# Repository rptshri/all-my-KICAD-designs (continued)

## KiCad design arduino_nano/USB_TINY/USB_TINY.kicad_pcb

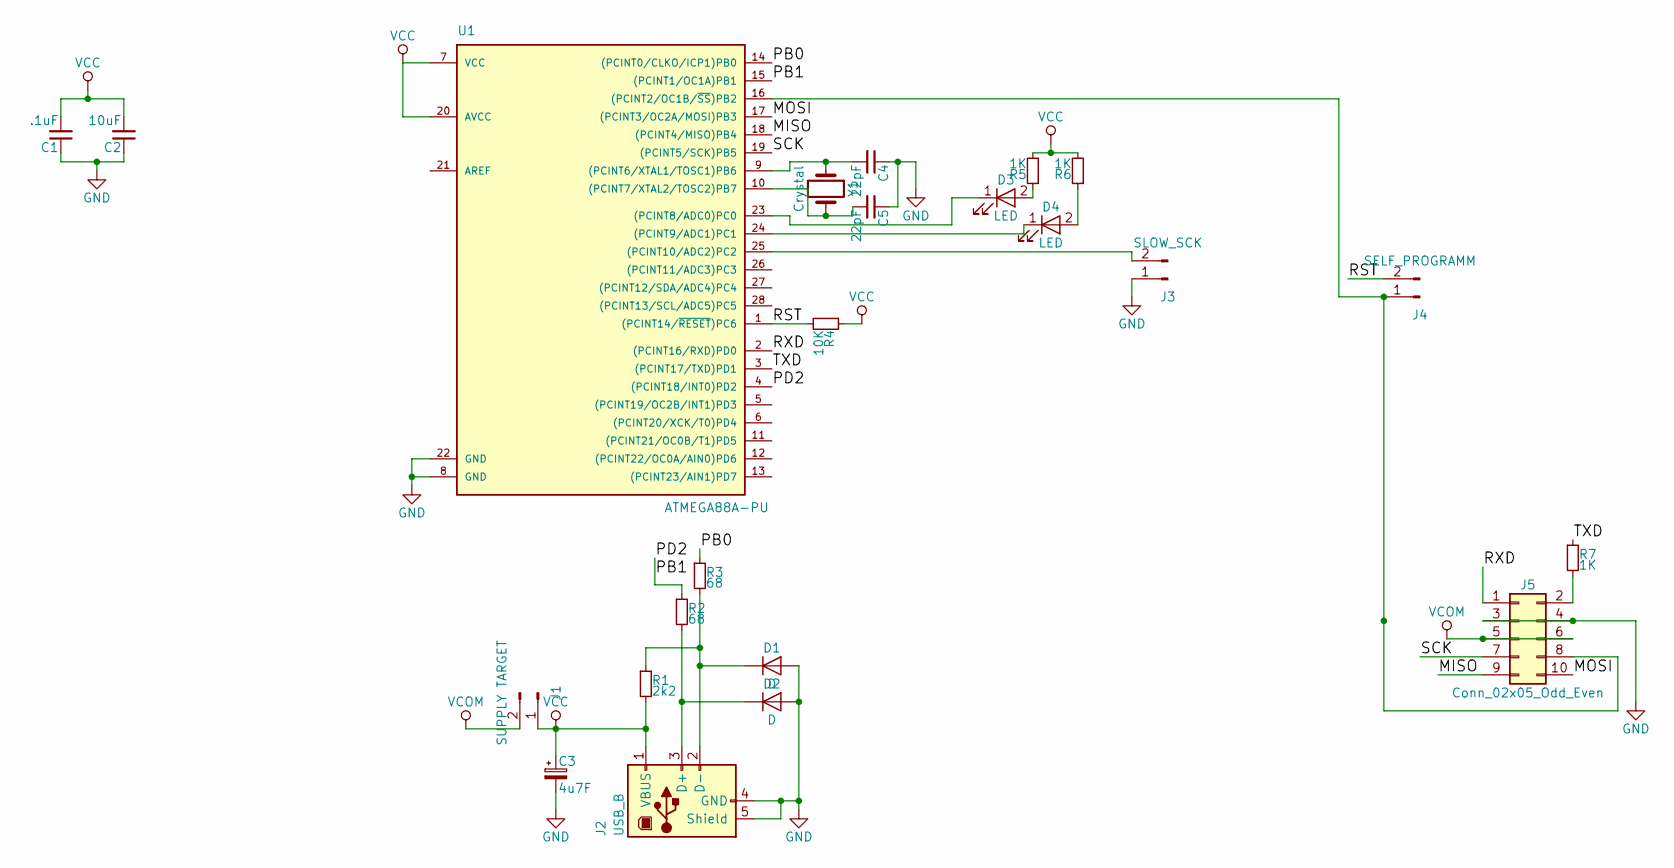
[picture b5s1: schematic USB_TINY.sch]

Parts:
C1: .1uF; C_Disc_D3.4mm_W2.1mm_P2.50mm
C2: 10uF; C_Disc_D3.4mm_W2.1mm_P2.50mm
C3: 4u7F; CP_Radial_D4.0mm_P2.00mm
C4, C5: 22pF; C_Disc_D3.0mm_W2.0mm_P2.50mm
D1, D2: D; D_A-405_P7.62mm_Horizontal
D3, D4: LED; LED_D3.0mm
J1: SUPPLY TARGET; Pin_Header_Straight_1x02_Pitch2.54mm
J2: USB_B
J3: SLOW_SCK; Pin_Header_Straight_1x02_Pitch2.54mm
J4: SELF_PROGRAMM; Pin_Header_Straight_1x02_Pitch2.54mm
J5: Conn_02x05_Odd_Even; Pin_Header_Straight_2x05_Pitch2.54mm
R1: 2k2; R_Axial_DIN0207_L6.3mm_D2.5mm_P7.62mm_Horizontal
R2, R3: 68; R_Axial_DIN0207_L6.3mm_D2.5mm_P7.62mm_Horizontal
R4: 10K; R_Axial_DIN0207_L6.3mm_D2.5mm_P7.62mm_Horizontal
R5, R6, R7: 1K; R_Axial_DIN0207_L6.3mm_D2.5mm_P7.62mm_Horizontal
U1: ATMEGA88A-PU; DIP-28_W7.62mm_LongPads
Y1: Crystal; Crystal_HC18-U_Vertical

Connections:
/MISO: J5.9, U1.18 ((PCINT4/MISO)PB4)
/MOSI: J5.10, U1.17 ((PCINT3/OC2A/MOSI)PB3)
/PB0: R3.1, U1.14 ((PCINT0/CLKO/ICP1)PB0)
/PB1: R2.1, U1.4 ((PCINT18/INT0)PD2), U1.15 ((PCINT1/OC1A)PB1)
/RST: J4.2, R4.2, U1.1 ((PCINT14/~RESET~)PC6)
/RXD: J5.1, U1.2 ((PCINT16/RXD)PD0)
/SCK: J5.7, U1.19 ((PCINT5/SCK)PB5)
/TXD: R7.1, U1.3 ((PCINT17/TXD)PD1)
GND: C1.1, C2.1, C3.2, C4.1, C5.1, D1.2 (A), D2.2 (A), J2.4 (GND), J2.5 (Shield), J3.1, J5.3, J5.4, U1.8 (GND), U1.22 (GND)
unnamed: C4.2, U1.9 ((PCINT6/XTAL1/TOSC1)PB6), Y1.1
unnamed: C5.2, U1.10 ((PCINT7/XTAL2/TOSC2)PB7), Y1.2
unnamed: D1.1 (K), J2.2 (D-), R1.1, R3.2
unnamed: D2.1 (K), J2.3 (D+), R2.2
unnamed: D3.1 (K), U1.23 ((PCINT8/ADC0)PC0)
unnamed: D3.2 (A), R5.1
unnamed: D4.1 (K), U1.24 ((PCINT9/ADC1)PC1)
unnamed: D4.2 (A), R6.1
unnamed: J3.2, U1.25 ((PCINT10/ADC2)PC2)
unnamed: J4.1, J5.8, U1.16 ((PCINT2/OC1B/~SS~)PB2)
unnamed: J5.2, R7.2
VCC: C1.2, C2.2, C3.1, J1.1, J2.1 (VBUS), R1.2, R4.1, R5.2, R6.2, U1.7 (VCC), U1.20 (AVCC)
VCOM: J1.2, J5.5, J5.6

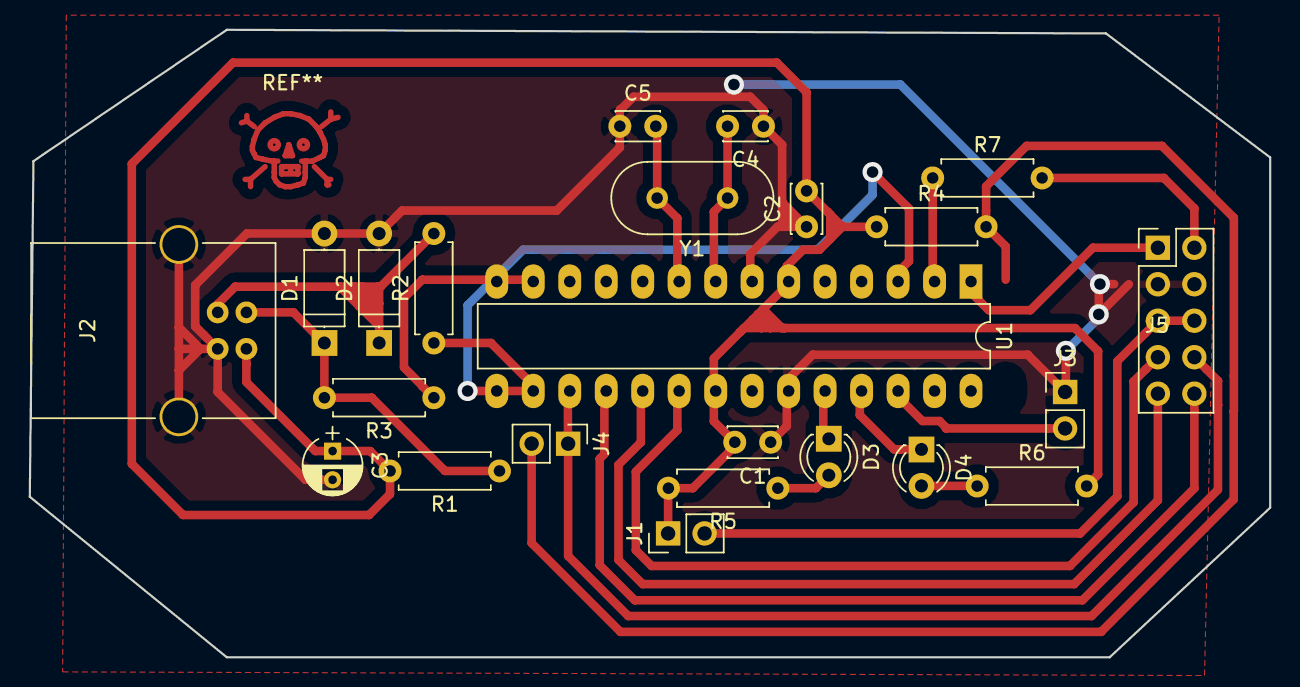
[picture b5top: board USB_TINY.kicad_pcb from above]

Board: 2 copper layers, 86.4 x 43.7 mm, 23 parts (0 on the bottom side), 22 nets.

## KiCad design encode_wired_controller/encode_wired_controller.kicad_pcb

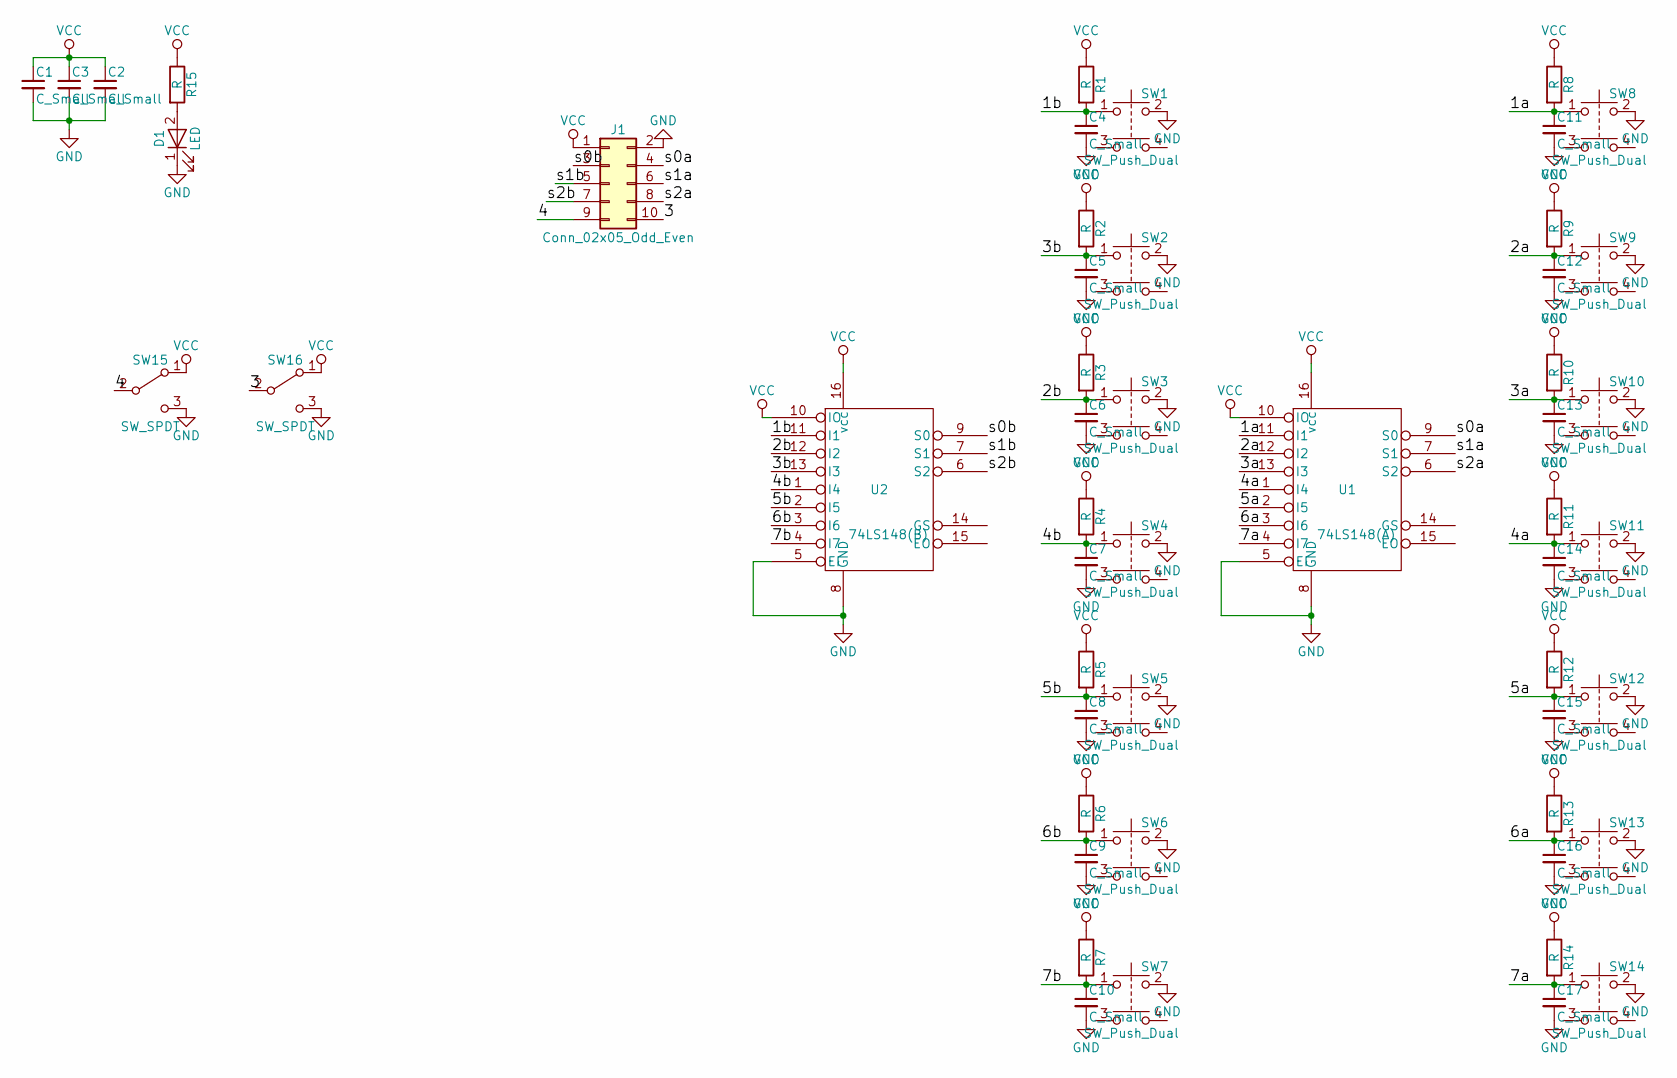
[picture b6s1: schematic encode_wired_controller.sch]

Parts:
C1, C2, C3, C4, C5, C6, C7, C8, C9, C10, C11, C12, C13, C14, C15, C16, C17: C_Small; C_Disc_D3.4mm_W2.1mm_P2.50mm
D1: LED; LED_D5.0mm_FlatTop
J1: Conn_02x05_Odd_Even; Pin_Header_Angled_2x05_Pitch2.54mm
R1, R2, R3, R4, R5, R6, R7, R8, R9, R10, R11, R12, R13, R14, R15: R; R_Axial_DIN0207_L6.3mm_D2.5mm_P7.62mm_Horizontal
SW1, SW2, SW3, SW4, SW5, SW6, SW7, SW8, SW9, SW10, SW11, SW12, SW13, SW14: SW_Push_Dual; SW_PUSH_6mm_h5mm
SW15, SW16: SW_SPDT; SW_E-Switch_EG1224_SPDT_Angled
U1: 74LS148(A); DIP-16_W7.62mm_LongPads
U2: 74LS148(B); DIP-16_W7.62mm_LongPads

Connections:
/1a: C11.1, R8.2, SW8.1, U1.11 (I1)
/1b: C4.1, R1.2, SW1.1, U2.11 (I1)
/2a: C12.1, R9.2, SW9.1, U1.12 (I2)
/2b: C6.1, R3.2, SW3.1, U2.12 (I2)
/3: J1.10, SW16.2 (B)
/3a: C13.1, R10.2, SW10.1, U1.13 (I3)
/3b: C5.1, R2.2, SW2.1, U2.13 (I3)
/4: J1.9, SW15.2 (B)
/4a: C14.1, R11.2, SW11.1, U1.1 (I4)
/4b: C7.1, R4.2, SW4.1, U2.1 (I4)
/5a: C15.1, R12.2, SW12.1, U1.2 (I5)
/5b: C8.1, R5.2, SW5.1, U2.2 (I5)
/6a: C16.1, R13.2, SW13.1, U1.3 (I6)
/6b: C9.1, R6.2, SW6.1, U2.3 (I6)
/7a: C17.1, R14.2, SW14.1, U1.4 (I7)
/7b: C10.1, R7.2, SW7.1, U2.4 (I7)
/s0a: J1.4, U1.9 (S0)
/s0b: J1.3, U2.9 (S0)
/s1a: J1.6, U1.7 (S1)
/s1b: J1.5, U2.7 (S1)
/s2a: J1.8, U1.6 (S2)
/s2b: J1.7, U2.6 (S2)
GND: C1.2, C2.2, C3.2, C4.2, C5.2, C6.2, C7.2, C8.2, C9.2, C10.2, C11.2, C12.2, C13.2, C14.2, C15.2, C16.2, C17.2, D1.1 (K), J1.2, SW1.2, SW2.2, SW3.2, SW4.2, SW5.2, SW6.2, SW7.2, SW8.2, SW9.2, SW10.2, SW11.2, SW12.2, SW13.2, SW14.2, SW15.3 (C), SW16.3 (C), U1.5 (EI), U1.8 (GND), U2.5 (EI), U2.8 (GND)
unnamed: D1.2 (A), R15.2
VCC: C1.1, C2.1, C3.1, J1.1, R1.1, R2.1, R3.1, R4.1, R5.1, R6.1, R7.1, R8.1, R9.1, R10.1, R11.1, R12.1, R13.1, R14.1, R15.1, SW15.1 (A), SW16.1 (A), U1.10 (IO), U1.16 (VCC), U2.10 (IO), U2.16 (VCC)

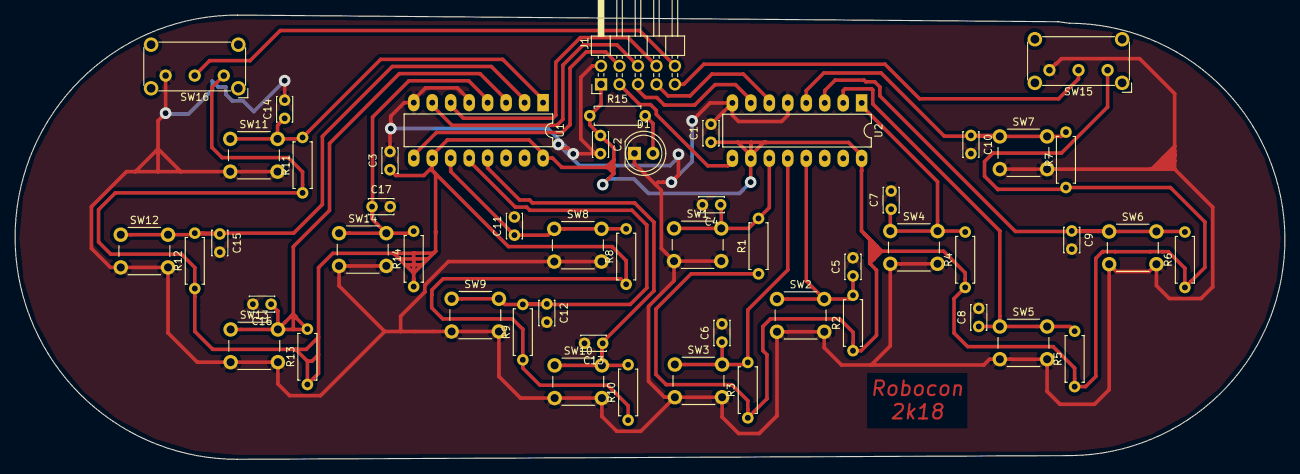
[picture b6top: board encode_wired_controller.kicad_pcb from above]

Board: 2 copper layers, 174.6 x 61.1 mm, 52 parts (0 on the bottom side), 25 nets.

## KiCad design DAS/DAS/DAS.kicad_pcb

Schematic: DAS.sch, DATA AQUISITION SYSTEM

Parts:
C1: 1500uF; CP_Radial_D4.0mm_P2.00mm
C2: .33uF; C_Disc_D3.0mm_W2.0mm_P2.50mm
C3, C8: .1uF; C_Disc_D3.0mm_W2.0mm_P2.50mm
C4: 440uF; CP_Radial_D4.0mm_P2.00mm
C5, C6: 22pF; C_Disc_D3.0mm_W2.0mm_P2.50mm
C7: 220uF; CP_Radial_D4.0mm_P2.00mm
C9, C10, C11, C12, C13: 1uF; C_Disc_D3.0mm_W2.0mm_P2.50mm
DS1: WC1602A; Pin_Header_Straight_1x16_Pitch2.54mm
J1: Screw_Terminal_01x03; TerminalBlock_bornier-3_P5.08mm
J2: Pressure Sensor; Pin_Header_Straight_1x03_Pitch2.54mm
J3: AVR-ISP-6; Pin_Header_Straight_2x03_Pitch2.54mm
J4: DB9_Female_MountingHoles; DSUB-9_Male_Horizontal_Pitch2.77x2.84mm_EdgePinOffset4.94mm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
R1: 6.67K; R_Axial_DIN0204_L3.6mm_D1.6mm_P5.08mm_Horizontal
R2: 20K; R_Axial_DIN0204_L3.6mm_D1.6mm_P5.08mm_Horizontal
R3, R8: 10k; R_Axial_DIN0204_L3.6mm_D1.6mm_P5.08mm_Horizontal
R4, R11: 1k; R_Axial_DIN0204_L3.6mm_D1.6mm_P5.08mm_Horizontal
R5: 10K; R_Axial_DIN0204_L3.6mm_D1.6mm_P5.08mm_Horizontal
R6: 5K; R_Axial_DIN0204_L3.6mm_D1.6mm_P5.08mm_Horizontal
R7: 2.33k; R_Axial_DIN0204_L3.6mm_D1.6mm_P5.08mm_Horizontal
R9: 10k; R_0805_HandSoldering
R10: 270; R_0805_HandSoldering
RV1: R_POT; Potentiometer_Alps_RK09Y_Vertical
SW1: SW_Push; SW_PUSH_6mm
U1: LM35-LP; TO-92_Inline_Narrow_Oval
U2, U4, U5: OP07; DIP-8_W7.62mm_Socket_LongPads
U3: L7805; TO-220-3_Vertical
U6: PIC18F452-IP; DIP-40_W15.24mm_LongPads
U7: MAX232; DIP-16_W7.62mm_Socket_LongPads
Y1: 8MHz; Crystal_HC18-U_Vertical

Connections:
+5V: C3.1, C4.1, C7.1, C8.1, C9.1, DS1.2, J2.1, J3.2, R9.1, R11.1, RV1.3, U1.1, U3.3, U6.11 (VDD), U6.32 (VDD), U7.16
+12V: C1.1, C2.1, J1.3, U2.7, U3.1, U4.7, U5.7
-12V: J1.1, U2.4, U4.4, U5.4
/AN0: R7.1, U4.6, U6.2 (RA0/AN0)
/AN1: R8.1, U5.6, U6.3 (RA1/AN1)
/DB0: DS1.7, U6.19 (PSP0/RD0)
/DB1: DS1.8, U6.20 (PSP1/RD1)
/DB2: DS1.9, U6.21 (PSP2/RD2)
/DB3: DS1.10, U6.22 (PSP3/RD3)
/DB4: DS1.11, U6.27 (PSP4/RD4)
/DB5: DS1.12, U6.28 (PSP5/RD5)
/DB6: DS1.13, U6.29 (PSP6/RD6)
/DB7: DS1.14, U6.30 (PSP7/RD7)
/E: DS1.6, U6.17 (CCP1/RC2)
/MISO: J3.1, U6.24 (SDO/RC5)
/MOSI: J3.4, U6.23 (SDI/SDA/RC4)
/R-W: DS1.5, U6.16 (CCP2/T1OSI/RC1)
/RS: DS1.4, U6.15 (T10S0/T1CKI/RC0)
/RST: J3.5, R10.1, U6.1 (~MCLR~/VPP)
/RX_H: J4.2, U7.13
/RX_L: U6.26 (RX/DT/RC7), U7.12
/SCK: J3.3, U6.18 (SCK/SCL/RC3)
/TX_H: J4.3, U7.14
/TX_L: U6.25 (TX/CK/RC6), U7.11
GND: C1.2, C2.2, C3.2, C4.2, C5.2, C6.2, C7.2, C8.2, C9.2, C12.1, C13.1, DS1.1, DS1.16, J1.2, J2.3, J3.6, J4.0, J4.5, R1.2, R4.2, R6.2, RV1.1, SW1.1, U1.3, U3.2, U6.12 (VSS), U6.31 (VSS), U7.15
unnamed: C5.1, U6.14 (RA6/OSC2/CLKO), Y1.1
unnamed: C6.1, U6.13 (OSC1/CLKIN), Y1.2
unnamed: C10.1, U7.1
unnamed: C10.2, U7.3
unnamed: C11.1, U7.4
unnamed: C11.2, U7.5
unnamed: C12.2, U7.2
unnamed: C13.2, U7.6
unnamed: DS1.3, RV1.2
unnamed: DS1.15, R11.2
unnamed: J2.2, R2.2
unnamed: R1.1, U2.3
unnamed: R2.1, R3.2, U2.2
unnamed: R3.1, R5.2, U2.6
unnamed: R4.1, R7.2, U4.2
unnamed: R5.1, R8.2, U5.2
unnamed: R6.1, U5.3
unnamed: R9.2, R10.2, SW1.2
unnamed: U1.2, U4.3

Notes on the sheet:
INPUT STAGE
+12V TO +5V
PRESSURE WITH SIGNAL CONDITIONING
LM35 WITH SIGNAL CONDITIONING
PIC18F452 MICROCONTROLLER
DISPLAY CIRCUIT
ISP HEADER
TTL TO RS232 CONVERSION CIRCUIT
DB9 CONNECTOR

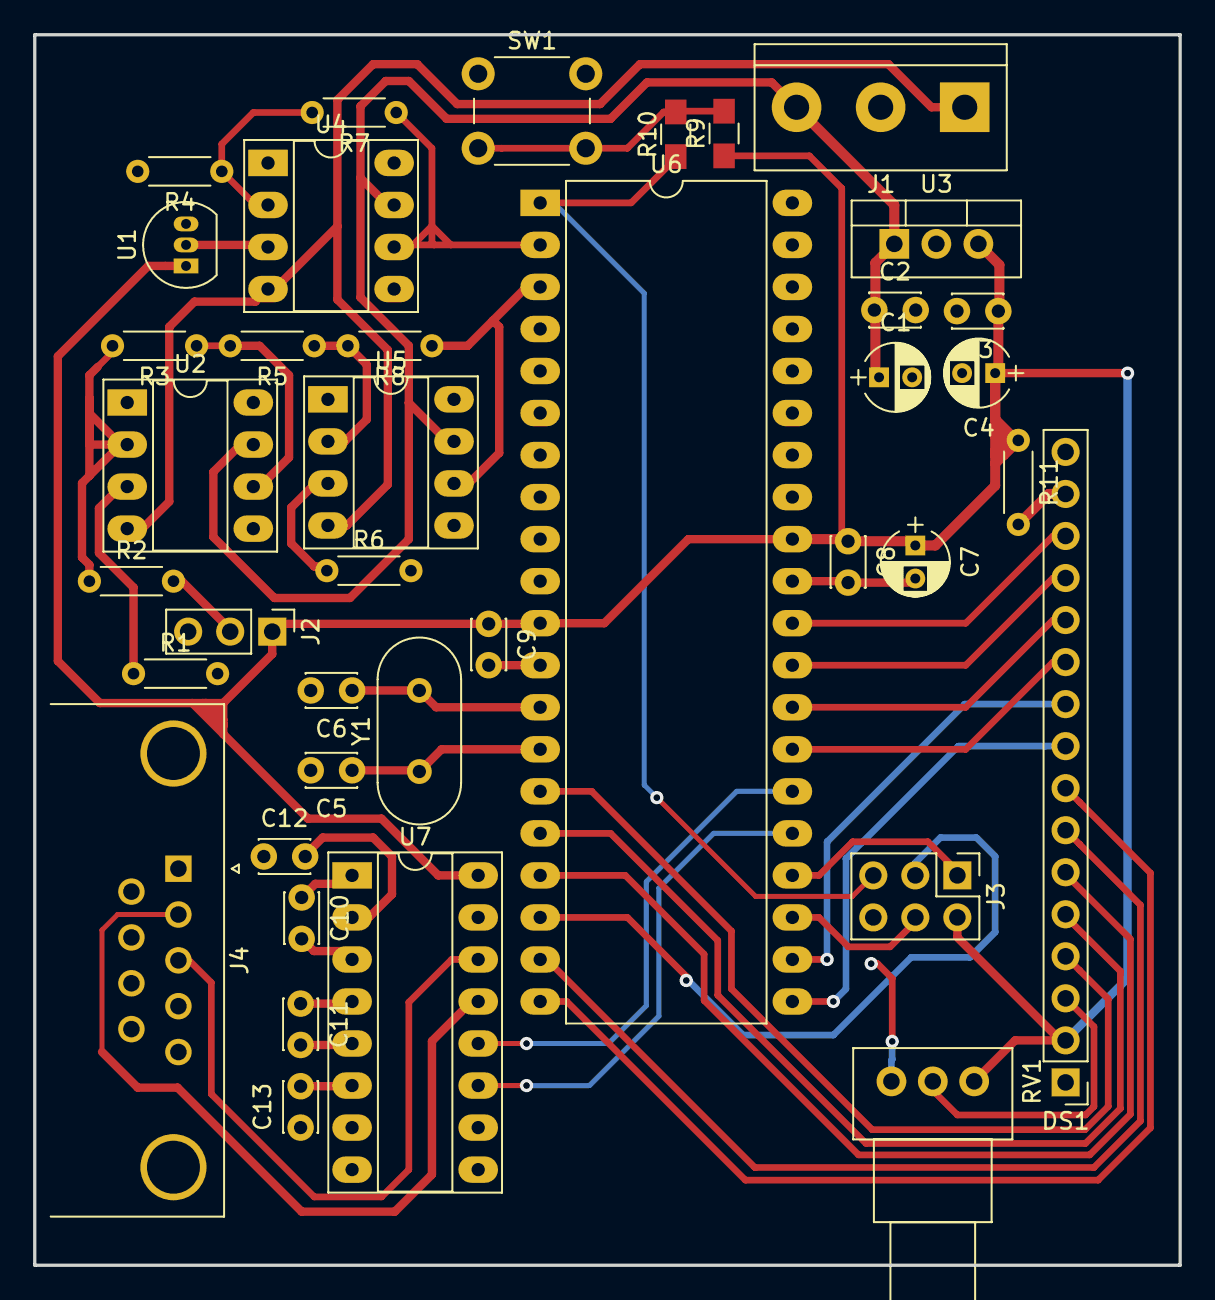
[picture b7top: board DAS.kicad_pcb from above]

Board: 2 copper layers, 69.2 x 74.4 mm, 39 parts (0 on the bottom side), 44 nets.

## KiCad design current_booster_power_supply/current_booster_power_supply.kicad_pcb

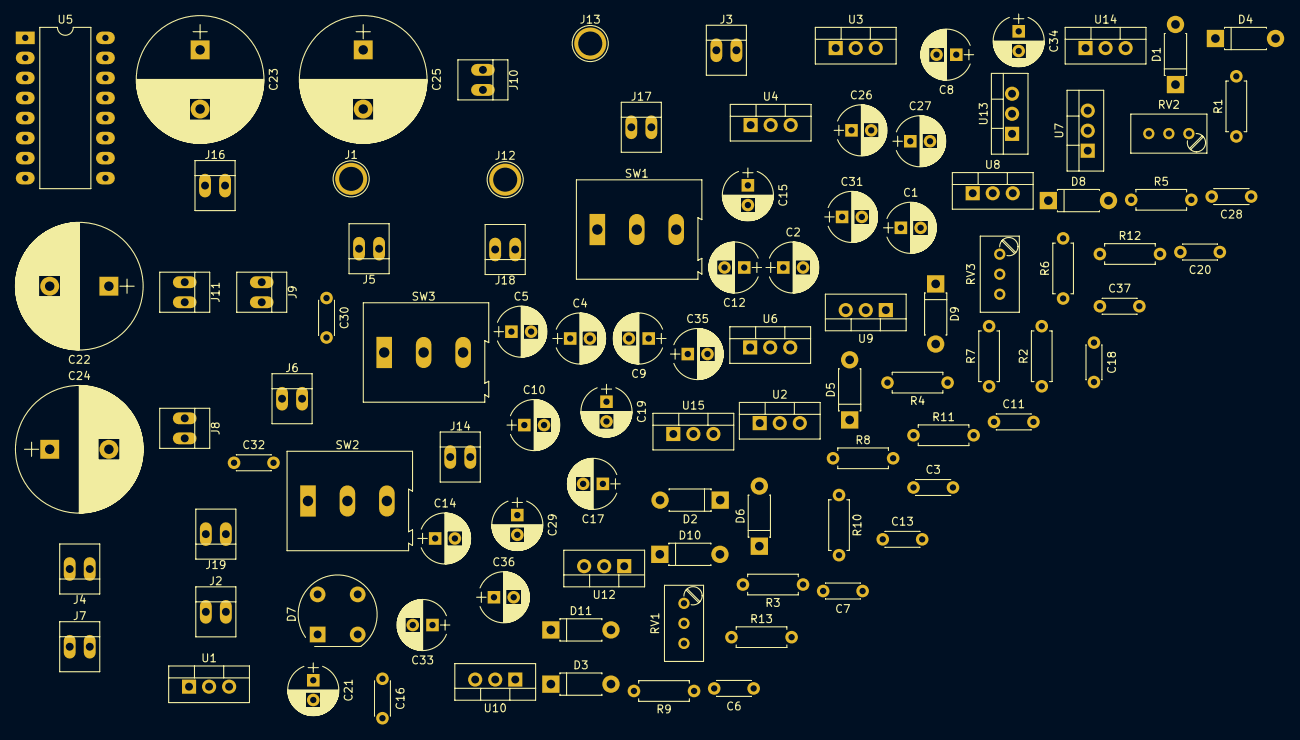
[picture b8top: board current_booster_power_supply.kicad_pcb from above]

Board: 2 copper layers, 99 parts (0 on the bottom side), 27 nets, no tracks yet.

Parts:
C1, C4, C8, C9, C10, C14, C15, C17, C19, C29, C31, C36: CP; CP_Radial_D6.3mm_P2.50mm
C2: C; CP_Radial_D6.3mm_P2.50mm
C3, C6, C7, C11, C13, C16, C18, C28, C30, C32, C37: C; C_Disc_D4.3mm_W1.9mm_P5.00mm
C5, C12, C33, C34, C35: 10uF; CP_Radial_D6.3mm_P2.50mm
C20: .47nf; C_Disc_D4.3mm_W1.9mm_P5.00mm
C21: .33uf; CP_Radial_D6.3mm_P2.50mm
C22, C23, C24, C25: 2200uF; CP_Radial_D16.0mm_P7.50mm
C26: .1uF; CP_Radial_D6.3mm_P2.50mm
C27: 1uF; CP_Radial_D6.3mm_P2.50mm
D1, D2, D3, D4, D5, D6, D8, D9, D10, D11: IN4001; D_DO-41_SOD81_P7.62mm_Horizontal
D7: D_Bridge_-A+A; Diode_Bridge_Round_D9.8mm
J1, J12, J13: Screw_Terminal_01x01; 1pin
J2, J3, J4, J5, J6, J7, J8, J9, J10, J11, J16, J17, J18, J19: Screw_Terminal_01x02; PINHEAD1-2
J14: OUT_TO_METER; PINHEAD1-2
R1, R2, R4, R6, R9, R11: 10; R_Axial_DIN0207_L6.3mm_D2.5mm_P7.62mm_Horizontal
R3: 310R; R_Axial_DIN0207_L6.3mm_D2.5mm_P7.62mm_Horizontal
R5, R7, R10, R13: 330R; R_Axial_DIN0207_L6.3mm_D2.5mm_P7.62mm_Horizontal
R8, R12: 2K046R; R_Axial_DIN0207_L6.3mm_D2.5mm_P7.62mm_Horizontal
RV1, RV2, RV3: POT_TRIM; Potentiometer_Trimmer_Bourns_3296W
SW1, SW2, SW3: SW_SPDT; TerminalBlock_Altech_AK300-3_P5.00mm
U1, U3, U4: LM317_3PinPackage; TO-220-3_Vertical
U2: L7805; TO-220-3_Vertical
U5: 4051; DIP-16_W10.16mm_LongPads
U6: AZ1117-ADJ; TO-220-3_Vertical
U7, U8, U12, U13: MJE2955T; TO-220-3_Vertical
U9, U14: MJE3055T; TO-220-3_Vertical
U10, U15: LM337_TO220; TO-220-3_Vertical

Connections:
+3V3: C21.1, J10.1, J11.1, U6.2
+5V: C7.1, C9.1, C20.1, C26.1, C27.1, J4.1, J5.1, SW1.1, SW2.1, SW3.1, U2.3, U5.16, U6.3, U8.3
+9V: C6.1, C8.1, D1.2, D2.1, J18.1, J19.1, R2.2, R3.1, U1.2, U7.3, U8.2
+12V: C23.1, C24.1, D7.3, R1.2, R4.2, R6.2, U7.2, U12.2, U13.2
-9VA: C36.2, C37.2, D10.1, D11.2, J2.1, J3.1, R13.2, U14.2, U15.3
-12VA: C22.2, C25.2, D7.1, R9.2, R11.2, U9.3, U14.3
/A: SW1.2, U5.11
/ADJ_2: C13.1, C14.1, D3.2, D4.1, J6.1, J7.1, R5.1, U3.2, U12.3
/ADJ_3: C18.1, C19.1, D5.2, D6.1, J8.1, J9.1, R7.1, U4.2, U13.3
/B: SW2.2, U5.10
/C: SW3.2, U5.9
/NEG_ADJ_1: C17.2, C28.2, D8.1, D9.2, J16.1, J17.1, R10.2, U9.2, U10.3
AC: D7.4, J1.1
GND: C1.2, C2.2, C3.2, C4.2, C5.2, C6.2, C7.2, C8.2, C9.2, C10.2, C11.2, C12.1, C13.2, C14.2, C15.1, C16.1, C17.1, C18.2, C19.2, C20.2, C21.2, C22.1, C23.2, C24.2, C25.1, C26.2, C27.2, C28.1, C29.2, C30.2, C31.1, C32.1, C33.2, C34.2, C35.1, C36.1, C37.1, J2.2, J3.2, J4.2, J5.2, J6.2, J7.2, J8.2, J9.2, J10.2, J11.2, J12.1, J14.2, J16.2, J17.2, J18.2, J19.2, R8.2, R12.1, RV1.1, RV2.3, RV3.3, SW1.3, SW2.3, SW3.3, U2.2, U5.6, U5.7, U5.8, U6.1
unnamed: C1.1, C2.1, D1.1, R1.1, U1.3, U7.1
unnamed: C3.1, C4.1, R2.1, U2.1, U8.1
unnamed: C5.1, D2.2, R3.2, R8.1, U1.1
unnamed: C10.1, C11.1, D3.1, R4.1, U3.3, U12.1
unnamed: C12.2, D9.1, R10.1, RV1.2, RV1.3, U10.1
unnamed: C15.2, C16.2, D8.2, R9.1, U9.1, U10.2
unnamed: C29.1, C30.1, D5.1, R6.1, U4.3, U13.1
unnamed: C31.2, C32.2, D10.2, R11.1, U14.1, U15.2
unnamed: C33.1, D4.2, R5.2, RV2.1, RV2.2, U3.1
unnamed: C34.1, D6.2, R7.2, RV3.1, RV3.2, U4.1
unnamed: C35.2, D11.1, R12.2, R13.1, U15.1
unnamed: J14.1, U5.3
VAC: D7.2, J13.1

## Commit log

2019-03-20 added files
2019-03-28 nightly_l298n
2019-03-28 updated doc
2019-03-29 l298_driver completed
2019-04-06 arduino board files update
2019-04-11 upadte project files
2019-06-27 UPADATE
2019-08-17 library update
2019-09-12 update logo
2019-10-12 Backlink to CADLAB.io has been added.
2019-12-27 Soic8+DIP8_hybrid
2020-05-25 [ImgBot] Optimize images
    *Total -- 3,964.41kb -> 2,680.25kb (32.39%)
    /l298_dRIVER/l298_dRIVER-Edge.Cuts.svg -- 1.02kb -> 0.52kb (49.14%)
    /l298_dRIVER/l298_dRIVER-F.Cu.svg -- 50.30kb -> 26.43kb (47.44%)
    /arduino_nano/USB_TINY/USB_TINY-F.Cu.svg -- 392.74kb -> 248.95kb (36.61%)
    /controller_board/_autosave-controller_board-F.Cu.svg -- 495.48kb -> 319.44kb (35.53%)
    /controller_board/controller_board-F.Cu.svg -- 185.88kb -> 124.07kb (33.25%)
